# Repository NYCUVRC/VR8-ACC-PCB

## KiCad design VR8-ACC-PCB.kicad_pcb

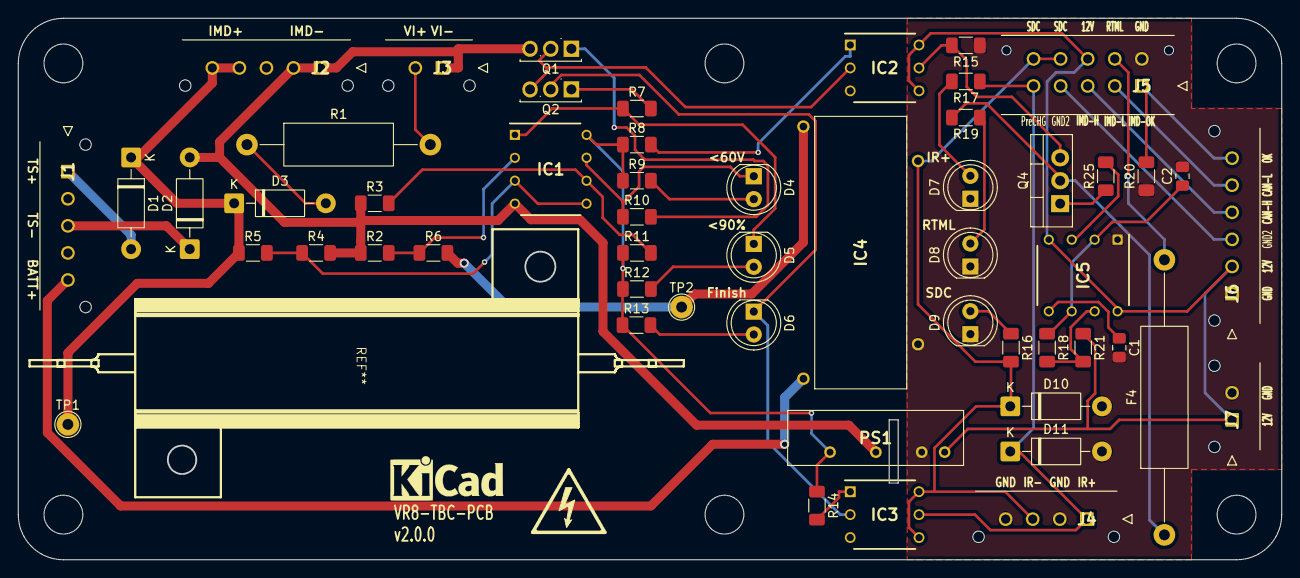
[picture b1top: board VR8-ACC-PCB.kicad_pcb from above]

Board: 2 copper layers, 139.9 x 59.9 mm, 60 parts (0 on the bottom side), 42 nets.

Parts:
C1: 0.01u; C_0805_2012Metric_Pad1.18x1.45mm_HandSolder
C2: 4.7u; C_0805_2012Metric_Pad1.18x1.45mm_HandSolder
D1, D2, D10, D11: 1N4007; D_DO-41_SOD81_P10.16mm_Horizontal
D3: 62V; D_DO-41_SOD81_P10.16mm_Horizontal
D4, D5, D6, D7, D8, D9: LED; LED_D5.0mm
F4: Fuse; R_Axial_DIN0516_L15.5mm_D5.0mm_P30.48mm_Horizontal
H1, H2, H3, H4, H5, H6: MountingHole; MountingHole_4.3mm_M4
IC1: LM393P; DIP794W53P254L959H508Q8N
IC2, IC3: VO14642AT; DIP762W60P254L760H470Q6N
IC4: KT12-1A-40L-THT; KT121A40LTHT
IC5: NE555P; DIP794W53P254L959H508Q8N
J1, J2: 43650-0516; 43650-05YY_151617
J3, J7: 43650-0216; 43650-02YY_151617
J4: 43650-0416; 43650-04YY_151617
J5: 43045-1013; 43045-10YY_121314
J6: 43650-0616; 43650-06YY_151617
PS1: SPU01M-12; SPU01M12
Q1, Q2: Q_NMOS_Depletion_GDS; TO-251-3_Vertical
Q4: Q_PMOS_GDS; TO-220-3_Vertical
R1: 200k; R_Axial_DIN0414_L11.9mm_D4.5mm_P20.32mm_Horizontal
R2: 51k; R_1206_3216Metric_Pad1.30x1.75mm_HandSolder
R3: 3.3k; R_1206_3216Metric_Pad1.30x1.75mm_HandSolder
R4: 56k; R_1206_3216Metric_Pad1.30x1.75mm_HandSolder
R5, R6: 3.3M; R_1206_3216Metric_Pad1.30x1.75mm_HandSolder
R7, R8, R9, R10, R12, R13, R14, R15, R16, R17, R19, R25: 10k; R_1206_3216Metric_Pad1.30x1.75mm_HandSolder
R11: 36k; R_1206_3216Metric_Pad1.30x1.75mm_HandSolder
R18: 47k; R_1206_3216Metric_Pad1.30x1.75mm_HandSolder
R20: 2.2k; R_1206_3216Metric_Pad1.30x1.75mm_HandSolder
R21: 1k; R_1206_3216Metric_Pad1.30x1.75mm_HandSolder
TP1, TP2: TestPoint; TestPoint_THTPad_D2.5mm_Drill1.2mm

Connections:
BATT+: IC4.2 (COM), J1.5
Chassis_Ground: J5.4, J6.3
GLV_12V: IC2.4 (S'), IC2.6 (S), IC5.4 (RESET), IC5.8 (VCC), J5.8, J6.2, J7.1, PS1.1 (+VIN), R21.1
GND: C1.2, C2.2, D7.1 (K), D8.1 (K), D9.1 (K), D10.2 (A), D11.2 (A), IC4.3 (COIL_1), IC5.1 (GND), J4.2, J4.4, J5.6, J6.1, J7.2, PS1.2 (-VIN), R15.1, R20.1
HV+: IC4.1 (NO), R6.2, TP2.1 (1_1)
HV_12V: IC1.8 (VCC), PS1.6 (+VOUT), R8.1, R9.1, R11.1, R12.1, R13.1, R14.1
IMD_CAN_H: J5.3, J6.4
IMD_CAN_L: J5.2, J6.5
IMD_Status: J5.1, J6.6, R20.2
IR+_ctrl: D11.1 (K), IC3.5 (DC), J4.1, J5.5, R17.1
unnamed: D1.2 (A), J1.1
unnamed: D2.1 (K), J1.3
unnamed: D3.2 (A), R1.1
unnamed: D4.2 (A), R9.2
unnamed: D5.2 (A), R12.2
unnamed: D6.2 (A), R13.2
unnamed: D6.1 (K), IC3.2 (K), Q2.2 (D)
unnamed: D7.2 (A), R17.2
unnamed: D8.2 (A), R19.1
unnamed: D9.2 (A), R16.1
unnamed: IC1.3 (1IN+), IC1.5 (2IN+), R4.1, R5.2
unnamed: IC1.2 (1IN-), R2.2, R6.1
unnamed: IC1.6 (2IN-), R3.2, R11.2
unnamed: IC2.1 (A), R8.2
unnamed: IC2.2 (K), Q1.2 (D), Q2.3 (S)
unnamed: IC3.1 (A), R14.2
unnamed: C1.1, IC5.5 (CONT)
unnamed: IC5.7 (DISCH), R18.2, R21.2
unnamed: IC5.3 (OUT), R25.2
unnamed: C2.1, IC5.2 (TRIG), IC5.6 (THRES), R18.1
unnamed: Q1.1 (G), R10.2
unnamed: Q2.1 (G), R7.2
unnamed: F4.1, Q4.2 (D), R19.2
unnamed: Q4.1 (G), R25.1
OK_60V: D4.1 (K), IC1.7 (2OUT), R10.1
OK_90%: D5.1 (K), IC1.1 (1OUT), R7.1
RTML: F4.2, J5.7
RTML_enable: IC2.5 (DC), Q4.3 (S), R15.2
SDC_final: D10.1 (K), IC3.4 (S'), IC3.6 (S), IC4.4 (COIL_2), J4.3, J5.9, J5.10, R16.2
TS+: D1.1 (K), D3.1 (K), J2.4, J2.5, R5.1, TP1.1 (1_1)
TS-: D2.2 (A), IC1.4 (GND), J2.1, J2.2, J3.1, PS1.4 (-VOUT), Q1.3 (S), R2.1, R3.1, R4.2
VI+: J3.2, R1.2

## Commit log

2026-01-24 add some silkscreens
2026-01-24 add HV/LV boundary silkscreen
2026-01-24 add mouser part numbers
    change resisters footprints of 0805 to 1206 for 500V voltage rating
2026-01-24 Add images to README.md
2026-01-24 fix date
2026-01-24 J5 reorientation
2026-01-24 update images to README
2026-01-24 Initial plan
2026-01-24 Move tag v1.2.3 to latest commit with push script
2026-01-24 Final update: tag v1.2.3 moved to latest commit e68132c
2026-01-24 Use dynamic references in tag move documentation
2026-01-24 Address code review feedback: add confirmation prompt and remove hardcoded branch
2026-01-24 Fix duplicate warning message in push script
2026-01-25 J4 reorientation
2026-01-25 update version
2026-01-25 Update images in README.md
    Replaced images.
2026-01-27 add ne555 output resister
2026-02-15 fix wrong DCDC & precharge relay pin connection
    swap out +/out - of the DCDC
    swap coil/contact of the relay
2026-05-09 find and fix test errors, some improvement
    1. remove onboard fuse (now is inline)
    2. change RTML nmos to pmos (to make nmos on, RTML only have V_G-V_th=10V, which is not enough to drive RTML)
    3. new voltage divider config (resistors tolerance is matter, <1% is better)
    4. add IR+_ctrl signal output to J5
    5. J7 is now used for powering Arduino rather than bridging interlock signal (SDC_after_MSD is removed from J5 as well)
    6. explain the working principle on sch
2026-05-09 Update images in README.md
    Removed several images and added new images with updated dimensions and alt text.
2026-05-09 Replace old images with new ones in README.md
